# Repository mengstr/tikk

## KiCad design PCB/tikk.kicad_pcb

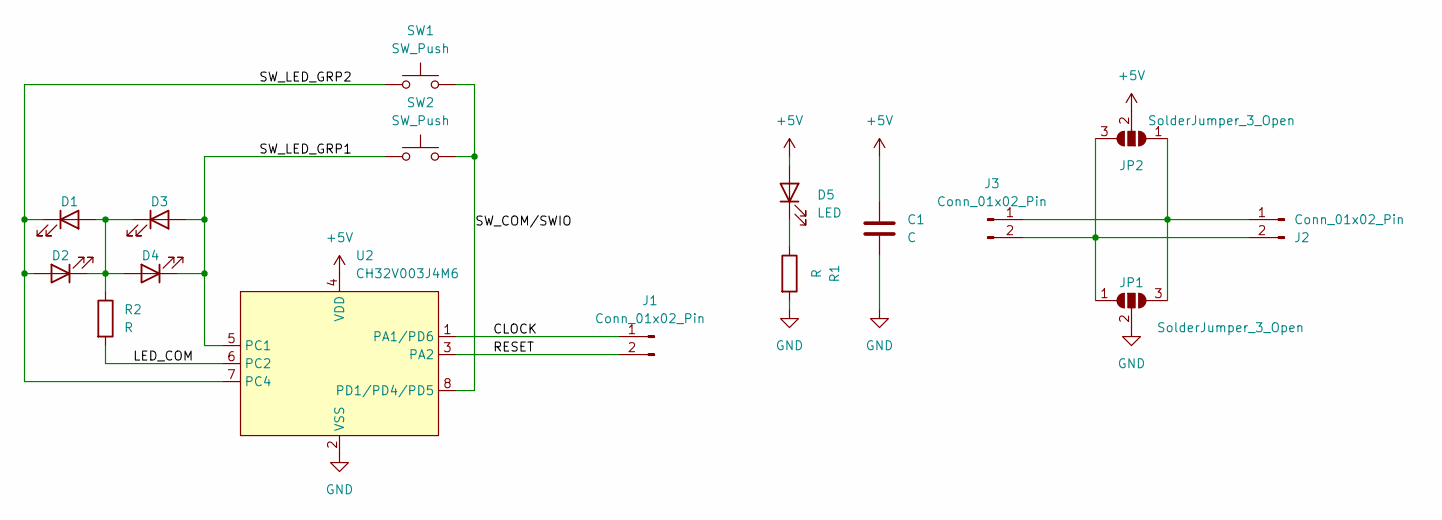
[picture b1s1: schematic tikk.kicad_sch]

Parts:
C1: C; C_0805_2012Metric_Pad1.18x1.45mm_HandSolder
D1, D2, D3, D4, D5: LED; LED_0805_2012Metric_Pad1.15x1.40mm_HandSolder
J1, J2, J3: Conn_01x02_Pin; PinHeader_1x02_P2.54mm_Vertical
JP1, JP2: SolderJumper_3_Open; SolderJumper-3_P1.3mm_Open_RoundedPad1.0x1.5mm
R1, R2: R; R_0805_2012Metric_Pad1.20x1.40mm_HandSolder
SW1, SW2: SW_Push; SW_Tactile_SPST_NO_Straight_CK_PTS636Sx25SMTRLFS
U2: CH32V003J4M6; SOIC-8_3.9x4.9mm_P1.27mm

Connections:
+5V: C1.1, D5.2 (A), JP2.2 (C), U2.4 (VDD)
/CLOCK: J1.1, U2.1 (PA1/PD6)
/LED_COM: R2.2, U2.6 (PC2)
/RESET: J1.2, U2.3 (PA2)
/SW_COM/SWIO: SW1.2, SW2.2, U2.8 (PD1/PD4/PD5)
/SW_LED_GRP1: D3.2 (A), D4.1 (K), SW2.1, U2.5 (PC1)
/SW_LED_GRP2: D1.1 (K), D2.2 (A), SW1.1, U2.7 (PC4)
GND: C1.2, JP1.2 (C), R1.2, U2.2 (VSS)
unnamed: D1.2 (A), D2.1 (K), D3.1 (K), D4.2 (A), R2.1
unnamed: D5.1 (K), R1.1
unnamed: J2.1, J3.1, JP1.3 (B), JP2.1 (A)
unnamed: J2.2, J3.2, JP1.1 (A), JP2.3 (B)

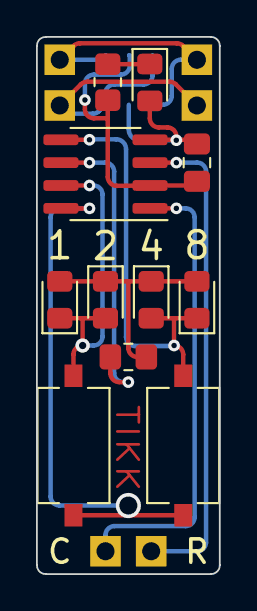
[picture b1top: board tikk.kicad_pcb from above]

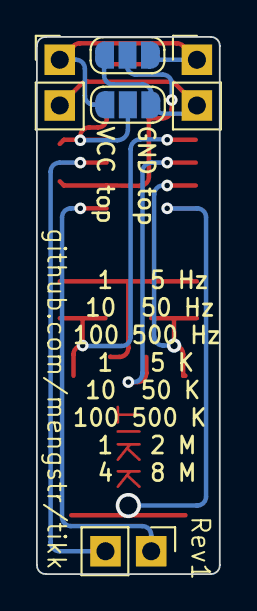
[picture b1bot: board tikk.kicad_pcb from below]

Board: 2 copper layers, 10.2 x 29.8 mm, 16 parts (5 on the bottom side), 12 nets.

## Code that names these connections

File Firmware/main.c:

#include "ch32v003fun/ch32v003fun.h"
#include "mcuflash.h"
#include "ports.h"

//
//       CH32V00J4M6 SOP8
// +----------+      +-----------+   		Pin1 PA1/T1CH2  --> 	Clock output
// |           \____/            |   	    Pin2            VSS
// |                             |          Pin3 PA2        --> 	Button common
// | PD6/PA1    PD4/PD5/SWIO/PD1 |   		Pin4            VDD
// | VSS                     PC4 |   		Pin5 PC1        --> 	LED pair1
// | PA2                     PC2 |          Pin6 PC2	    -->     LED pair2
// | VDD                     PC1 |          Pin7 PC4        --> 	Reset output
// |                             |          Pin8 PD4        <-- 	LED common(SWIO)
// +-----------------------------+
//

int data0;
int data1;

// --------------------------------------------------------
// data0 bit1-0 = reset mode
//		00 (0) = /reset, pulsed active at power up
//		01 (1) = reset, pulsed active at power up
//		10 (2) = /reset, held active until button pressed
//		11 (3) = reset, held active until button pressed
// --------------------------------------------------------
// data0 bit7-2 = frequency

#define FREQUENCIES 16

typedef struct frequency_T {
    int prescaler;
    int divider;
} frequency_T;

frequency_T frequencies[FREQUENCIES] = {
    {749, 63999}, //   1 Hz
    {149, 63999}, //   5 Hz
    {74, 63999},  //  10 Hz
    {14, 63999},  //  50 Hz
    {7, 59999},   // 100 Hz
    {1, 47999},   // 500 Hz
    {0, 47999},   //   1 KHz
    {0, 9599},    //   5 KHz
    {0, 4799},    //  10 KHz
    {0, 959},     //  50 KHz
    {0, 479},     // 100 KHz
    {0, 95},      // 500 KHz
    {0, 47},      //   1 MHz
    {0, 23},      //   2 MHz
    {0, 11},      //   4 MHz
    {0, 5},       //   8 MHz
};

#define LEFT_BUTTON 1
#define RIGHT_BUTTON 2

#define RESETBIT 4

void LEDbits(int common, int pair1, int pair2) {
    SetPortD(4, common);
    SetPortC(1, pair1);
    SetPortC(2, pair2);
}

void LEDoff() { LEDbits(FLOAT, FLOAT, FLOAT); }
void LED1() { LEDbits(LOW, HIGH, FLOAT); }
void LED2() { LEDbits(HIGH, LOW, FLOAT); }
void LED3() { LEDbits(LOW, FLOAT, HIGH); }
void LED4() { LEDbits(HIGH, FLOAT, LOW); }

int GetButtons() {
    LEDoff();
    SetPortA(2, PU); // Button Common
    int button = 0;

    SetPortC(1, LOW);
    SetPortC(2, FLOAT);
    Delay_Us(1);
    if (!(GPIOA->INDR & (1 << 2))) button |= 1;

    SetPortC(1, FLOAT);
    SetPortC(2, LOW);
    Delay_Us(1);
    if (!(GPIOA->INDR & (1 << 2))) button |= 2;

    LEDoff();
    SetPortA(2, FLOAT); // Button Common
    return button;
}

int BlinkLEDs(int pattern1, int pattern2) {
    int buttons;
    const int delay = 2;
    const int loops = 10;

    for (int i = 0; i < loops; i++) {

        if (pattern1 & 1) LED1();
        Delay_Ms(delay);
        buttons = GetButtons();
        if (buttons) return buttons;

        if (pattern1 & 2) LED2();
        Delay_Ms(delay);
        buttons = GetButtons();
        if (buttons) return buttons;

        if (pattern1 & 4) LED3();
        Delay_Ms(delay);
        buttons = GetButtons();
        if (buttons) return buttons;

        if (pattern1 & 8) LED4();
        Delay_Ms(delay);
        buttons = GetButtons();
        if (buttons) return buttons;
    }

    for (int i = 0; i < loops; i++) {
        if (pattern2 & 1) LED1();
        Delay_Ms(delay);
        buttons = GetButtons();
        if (buttons) return buttons;

        if (pattern2 & 2) LED2();
        Delay_Ms(delay);
        buttons = GetButtons();
        if (buttons) return buttons;

        if (pattern2 & 4) LED3();
        Delay_Ms(delay);
        buttons = GetButtons();
        if (buttons) return buttons;

        if (pattern2 & 8) LED4();
        Delay_Ms(delay);
        buttons = GetButtons();
        if (buttons) return buttons;
    }

    return 0;
}

void setFrequencyFromTable(int rate) {
    TIM1->PSC = frequencies[rate].prescaler;
    TIM1->ATRLR = frequencies[rate].divider;
    TIM1->CH2CVR = frequencies[rate].divider / 2;
    TIM1->SWEVGR |= TIM_UG;
}

// resetMode 0 :  /reset, pulsed active at power up
// resetMode 1 :  reset, pulsed active at power up
// resetMode 2 :  /reset, held active until button pressed
// resetMode 3 :  reset, held active until button pressed
void ActiveReset(int resetMode) {
    SetPortC(4, resetMode == 0 || resetMode == 2 ? LOW : HIGH);
}

void IdleReset(int resetMode) {
    SetPortC(4, resetMode == 0 || resetMode == 2 ? HIGH : LOW);
}

void SetupReset() {
    int timeout = 0;
    int resetMode = data0 & 0x03;

    // while (GetButtons() & RIGHT_BUTTON) BlinkLEDs(0x0F, 0);

    for (;;) {
        while (GetButtons() & RIGHT_BUTTON) {}
        int buttons = BlinkLEDs(1 << resetMode, 0);
        if (buttons & RIGHT_BUTTON) {
            timeout = 0;
            resetMode++;
            if (resetMode > 3) resetMode = 0;
        }
        if (timeout++ > 30) break;
    }

    data0 = (data0 & 0xfc) | resetMode;
    FlashOptionData(data0, data1);
}

int main() {
    SystemInit();

    // Enable GPIOA, GPIOC, GPIOD and TIM1
    RCC->APB2PCENR |= RCC_APB2Periph_GPIOA | RCC_APB2Periph_GPIOC |
                      RCC_APB2Periph_GPIOD | RCC_APB2Periph_TIM1;

    
    // Get and, if neccessary, initialise the stored settings
    data0 = OB->Data0;
    data1 = OB->Data1;
    if (data0 == 0xff || data1 == 0xff) {
        data0 = 0;
        data1 = 0;
        FlashOptionData(data0, data1);
    }


    int resetMode = data0 & 0x03;
    ActiveReset(resetMode);

    SetPortA(2, PU); // Button Common
    LEDoff();

    // PA1 is T1CH2, 50MHz Output alt func, push-pull
    GPIOA->CFGLR &= ~(0xf << (4 * 1));
    GPIOA->CFGLR |= (GPIO_Speed_50MHz | GPIO_CNF_OUT_PP_AF) << (4 * 1);

    RCC->APB2PRSTR |= RCC_APB2Periph_TIM1; // Reset TIM1 to init all regs
    RCC->APB2PRSTR &= ~RCC_APB2Periph_TIM1;
    TIM1->PSC = 65535;                 // Prescaler
    TIM1->ATRLR = 65535;               // Auto Reload - sets period
    TIM1->SWEVGR |= TIM_UG;            // Reload immediately
    TIM1->CCER |= TIM_CC2E | TIM_CC2P; // Enable CH2 output, positive pol
    TIM1->CHCTLR1 |=
        TIM_OC2M_2 |
        TIM_OC2M_1;         // CH2 Mode is output, PWM1 (CC1S = 00, OC1M = 110)
    TIM1->CH2CVR = 32768;   // Set the Capture Compare Register value to
                            // 50% initially
    TIM1->BDTR |= TIM_MOE;  // Enable TIM1 outputs
    TIM1->CTLR1 |= TIM_CEN; // Enable TIM1

    int rate = (data0 >> 2)&0x0f;
    setFrequencyFromTable(rate);
    // for (;;) {Delay_Ms(250);LED1();Delay_Ms(250);LED2();Delay_Ms(250);LED3();Delay_Ms(250);LED4();}

    if (GetButtons() & RIGHT_BUTTON) SetupReset();

    int inReset = 1;
    uint32_t sysTickEnd = SysTick->CNT + 6E6;
    for (;;) {

        if (inReset == 1) {
            int buttons = BlinkLEDs(5, 10);
            // Manual reset release mode
            if (resetMode >= 2) {
                if (buttons & RIGHT_BUTTON) {
                    IdleReset(resetMode);
                    Delay_Ms(100);
                    if (BlinkLEDs(0, 0) != 0) Delay_Ms(100);
                    inReset = 0;
                }
            } else {
                // Auto reset mode
                if (SysTick->CNT - sysTickEnd < 0x80000000UL) {
                    IdleReset(resetMode);
                    inReset = 0;
                }
            }
        }
        if (inReset == 2) {
            // reset button pressed mode
            BlinkLEDs(5, 10);
            if (SysTick->CNT - sysTickEnd < 0x80000000UL) {
                IdleReset(resetMode);
                inReset = 0;
            }
        }

        int buttons = GetButtons();

        if (buttons & RIGHT_BUTTON) {
            ActiveReset(resetMode);
            inReset = 2;
            sysTickEnd = SysTick->CNT + 6E6;
        }

        if (buttons & LEFT_BUTTON) {
            rate++;
            if (rate >= FREQUENCIES) rate = 0;
            setFrequencyFromTable(rate);
            data0=(data0&0x03)|(rate<<2);
            FlashOptionData(data0, data1);
            Delay_Ms(100);
            while (GetButtons()) {}
            Delay_Ms(100);
        }

        if (inReset == 0) BlinkLEDs(rate, rate);
    }
}

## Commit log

2023-09-20 PCB sent to JLCPCB. FW needs adapting to pin changes
